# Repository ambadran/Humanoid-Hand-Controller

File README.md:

# Humanoid-Hand-Controller

Interfacing muscle sensor V2 using micropython code 

(OPTIONAL BUT RECOMMENDED: Use AD7705 16-bit ADC to give more resolution and muscle activity range to play with)

The idea is to program a sequence of muscle intensities at specific time intervals which correlate to a specific `Movmement` python object

This `Movement` object can then be mapped to any actual transducer action you like. 

In this library it is assumed that the transducer is 5 servo motors each controlling a finger.

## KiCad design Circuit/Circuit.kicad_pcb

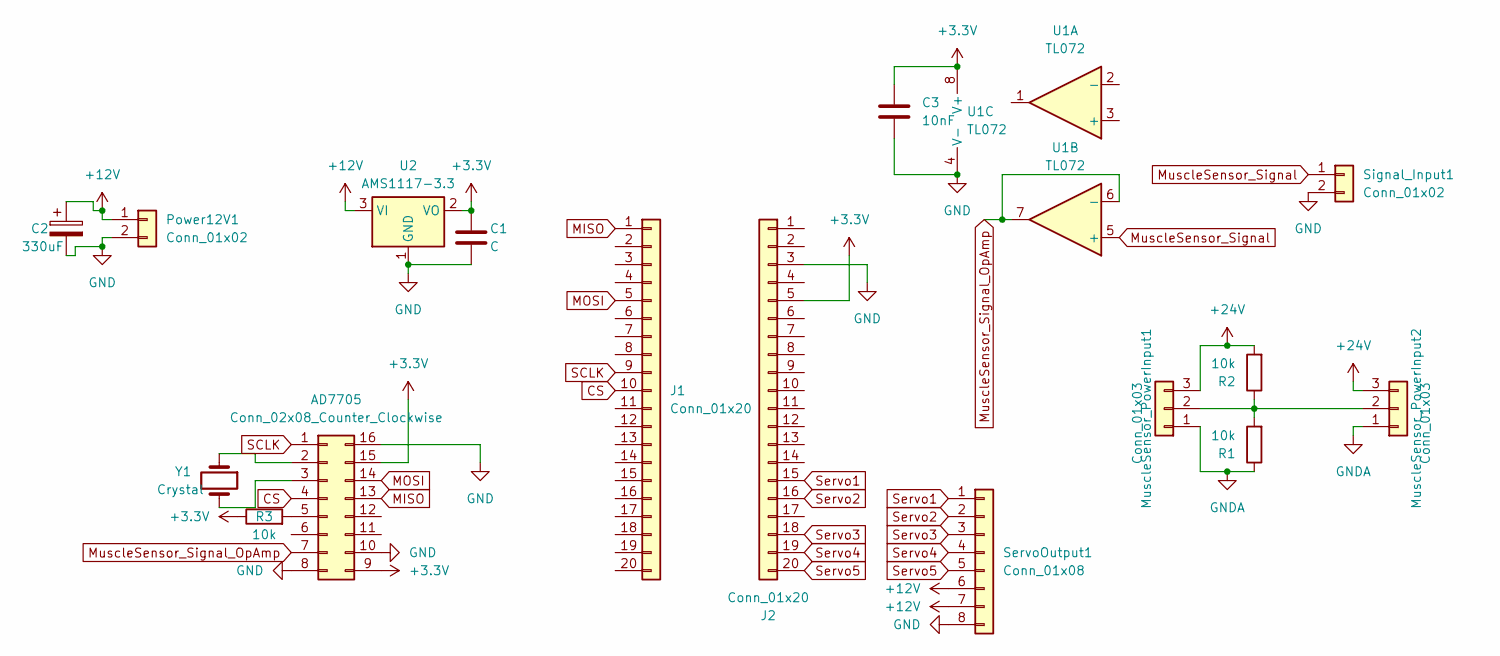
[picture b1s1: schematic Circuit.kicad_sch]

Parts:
AD7705: Conn_02x08_Counter_Clockwise; DIP-16_W7.62mm_LongPads
C1: C
C2: 330uF; CP_Radial_D8.0mm_P3.80mm
C3: 10nF; C_Disc_D5.0mm_W2.5mm_P5.00mm
J1, J2: Conn_01x20; PinSocket_1x20_P2.54mm_Vertical
MuscleSensor_PowerInput1: Conn_01x03; PinSocket_1x03_P2.54mm_Vertical
MuscleSensor_PowerInput2: Conn_01x03; JST_EH_S3B-EH_1x03_P2.50mm_Horizontal
Power12V1: Conn_01x02; JST_EH_B2B-EH-A_1x02_P2.50mm_Vertical
R1, R2, R3: 10k; R_Axial_DIN0207_L6.3mm_D2.5mm_P7.62mm_Horizontal
ServoOutput1: Conn_01x08; JST_EH_B8B-EH-A_1x08_P2.50mm_Vertical
Signal_Input1: Conn_01x02; PinSocket_1x02_P2.54mm_Vertical
U1: TL072; DIP-8_W7.62mm_Socket_LongPads
U2: AMS1117-3.3; TO-220-3_Vertical
Y1: Crystal; Crystal_HC49-4H_Vertical

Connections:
+3.3V: AD7705.9, AD7705.15, C1.2, C3.1, J2.5, R3.1, U1.8 (V+), U2.2 (VO)
+12V: C2.1, Power12V1.1, ServoOutput1.6, ServoOutput1.7, U2.3 (VI)
+24V: MuscleSensor_PowerInput1.3, MuscleSensor_PowerInput2.3, R2.2
CS: AD7705.4, J1.10
GND: AD7705.8, AD7705.10, AD7705.16, C1.1, C2.2, C3.2, J2.3, Power12V1.2, ServoOutput1.8, Signal_Input1.2, U1.4 (V-), U2.1 (GND)
GNDA: MuscleSensor_PowerInput1.1, MuscleSensor_PowerInput2.1, R1.1
MISO: AD7705.13, J1.1
MOSI: AD7705.14, J1.5
MuscleSensor_Signal: Signal_Input1.1, U1.5 (+)
MuscleSensor_Signal_OpAmp: AD7705.7, U1.6 (-), U1.7
unnamed: AD7705.2, Y1.1
unnamed: AD7705.3, Y1.2
unnamed: AD7705.5, R3.2
unnamed: MuscleSensor_PowerInput1.2, MuscleSensor_PowerInput2.2, R1.2, R2.1
SCLK: AD7705.1, J1.9
Servo1: J2.15, ServoOutput1.1
Servo2: J2.16, ServoOutput1.2
Servo3: J2.18, ServoOutput1.3
Servo4: J2.19, ServoOutput1.4
Servo5: J2.20, ServoOutput1.5

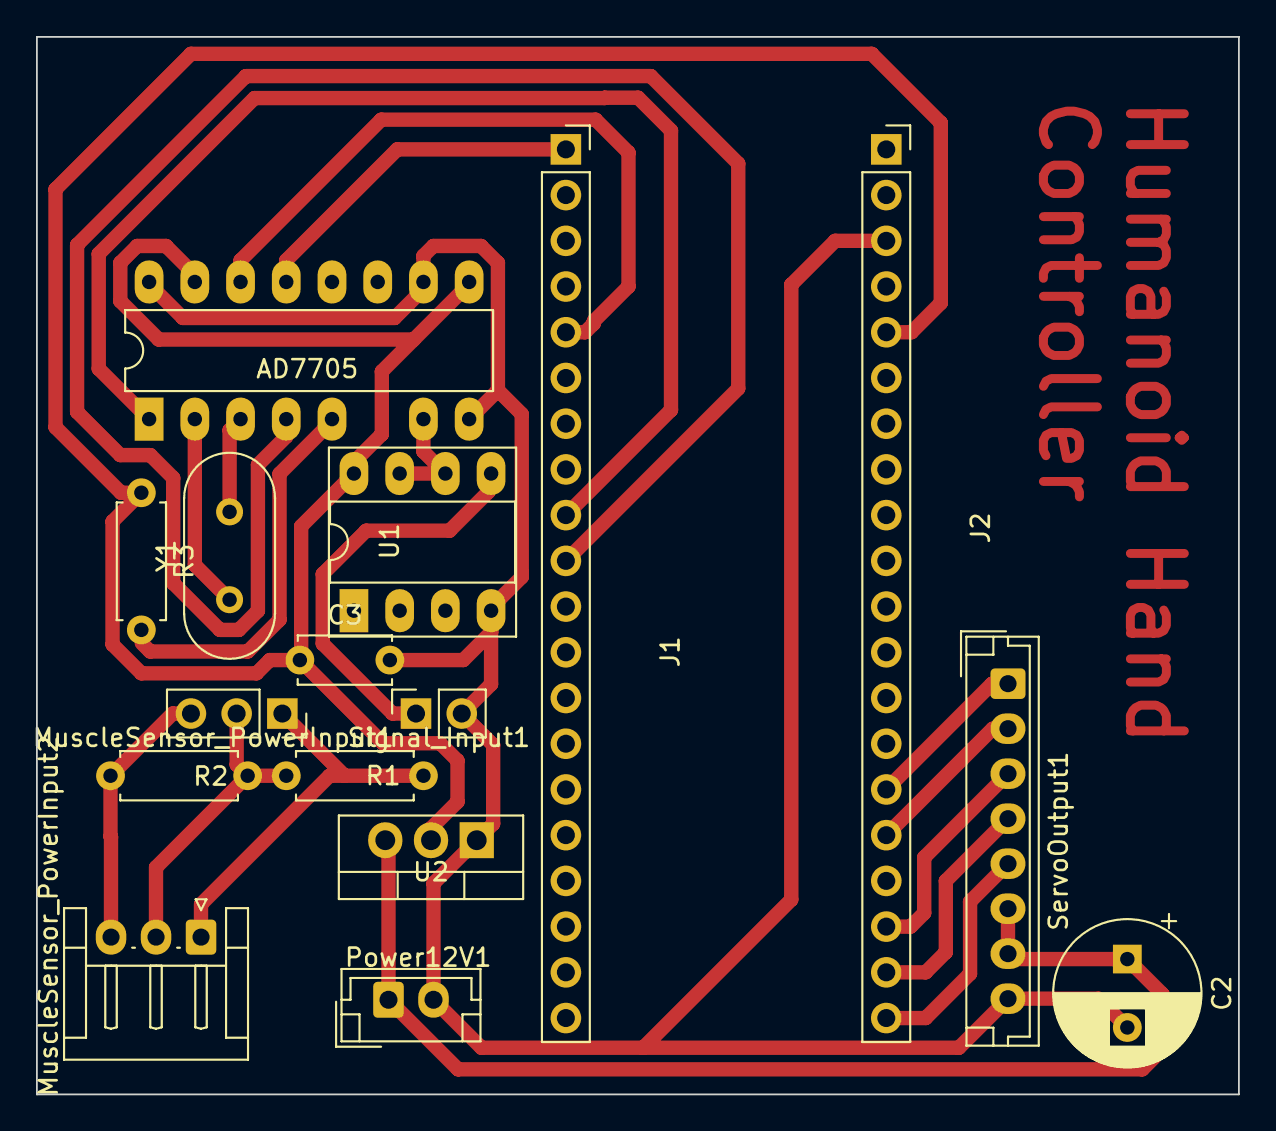
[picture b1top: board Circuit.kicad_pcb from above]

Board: 2 copper layers, 66.8 x 58.8 mm, 16 parts (0 on the bottom side), 20 nets.

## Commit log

2024-05-25 Working muscle_sensor V2 code tested and successful!
2024-05-25 finished PCB design, pending final distance measurements
2024-05-25 added BOM
2024-05-26 final PCB design done
2024-05-26 BOM done and minor changes
2024-05-28 minor bug fixes
2024-05-28 added calibration algorithm
2024-06-01 added OLED screen reporting
2024-06-02 added a switch and main.py to be work completly without a computer now
2024-06-04 added pcb step file
2024-06-04 Added Electronics Box 3D model partially finished
2024-06-04 finished 3D model of controller box with write mount
2024-06-08 added new BOM
2024-06-09 added a view raw ad value function by pressing button more than 1sec
2024-06-09 added full palm contraction Movement and read sequence is now persistent
2024-06-23 added delay for full hand contract function between each finger
